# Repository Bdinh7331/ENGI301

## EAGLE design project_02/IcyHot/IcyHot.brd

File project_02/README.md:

Author: Brian Dinh

The goal of this project was to create a PCB of my first project, IcyHot, were I have successfully completed it. Upon consulting with my professor, Erik Welsh, he suggested
that I add in the LED screen that I was unable to integrate during my first project. This project is associated with Rice University's Introduction to Practical Electrical
Engineering course, also known as ENGI 301.

This project uses the following libraries:
1. ENGI301, created by Erik Welsh
2. IcyHot, a custom library created by myself to house the Noctua fan and switch
3. adafruit, which came with EAGLE

To complete this project, I did the following steps:
1. Created a schematic using existing Pocketbeagle, LED screen, and temperature sensors from the three aforementioned libraries.
  -To create the nf-a4x20-5v-pwm (Noctua fan) component, I made a box with 4 pins that was about the physical dimensions of the base of the fan. Since the datasheet did not provide any additional information about how the pins were oriented, I spaced them out by about 100 mil.
  -To create the switch, I followed the exact guidelines provided by its datasheet.
2. Made a board on EAGLE using that schematic. This board was initially 3x4 as suggested by Professor Welsh, but I increased the dimensions to 3.5x4 to fit all of my components.
  -Because of how my components were organized in the board, I routed my components in the top and bottom layers instead of just the top layer.
  -I added as few drill holes as possible, though they were unavoidable because of how the routing was laid out on this board.
3. Prepared a gerber file for manufacturing
  -Exported my IcyHot.brd file as a CAM output, labelling it as "IcyHot_gerber."
  -Downloaded gerbv, an open source gerber reader, to provide a screenshot of the top and bottom layers of the PCB which is located in the "docs" folder of this directory.
  -Created an account at MacroFab.
4. Got quotes for 1, 10, 100, and 1000 PCBs with my components on MacroFab.
  -Substituted another 5V PWM fan for the Noctua because Noctua fans are not available on MacroFab. This affects the price though the fan was not the most expensive component.
  -Prices were much larger than expected since many of the components had very large lead times and/or were not immediately available.

Design Philosophy

  The design philosophy that I used during this project was essentially to keep everything as simple as possible since this is good engineering practice. Because the goal of this project was to put the components that I had used in the first ENGI 301 project onto a PCB, I wanted to replicate the exact components as much as possible. Some specific ways of how I ensured that the schematic would be simple was that I would only create library parts from scratch only when it was absolutely necessary. As several components had schematics, libraries, and boards already available on open source platforms it would be easier, and more accurate, for me to directly copy these materials onto my IcyHot schematic. Moreover, when I created components for the IcyHot library, I focused on making sure I had the necessary pins so that they could be correctly wired to the Pocketbeagle knowing that this wiring would be reflected in the IcyHot board. 
  Because the project's requirements included a second component in my IcyHot library, I chose to make a TPS92411x Floating Switch for Offline AC Linear Direct Drive of LEDs with Low Ripple Current because it paired well with my display screen. My thought was that it would "gatekeep" the voltage level in the system and if it were above a certain level the screen would turn off.

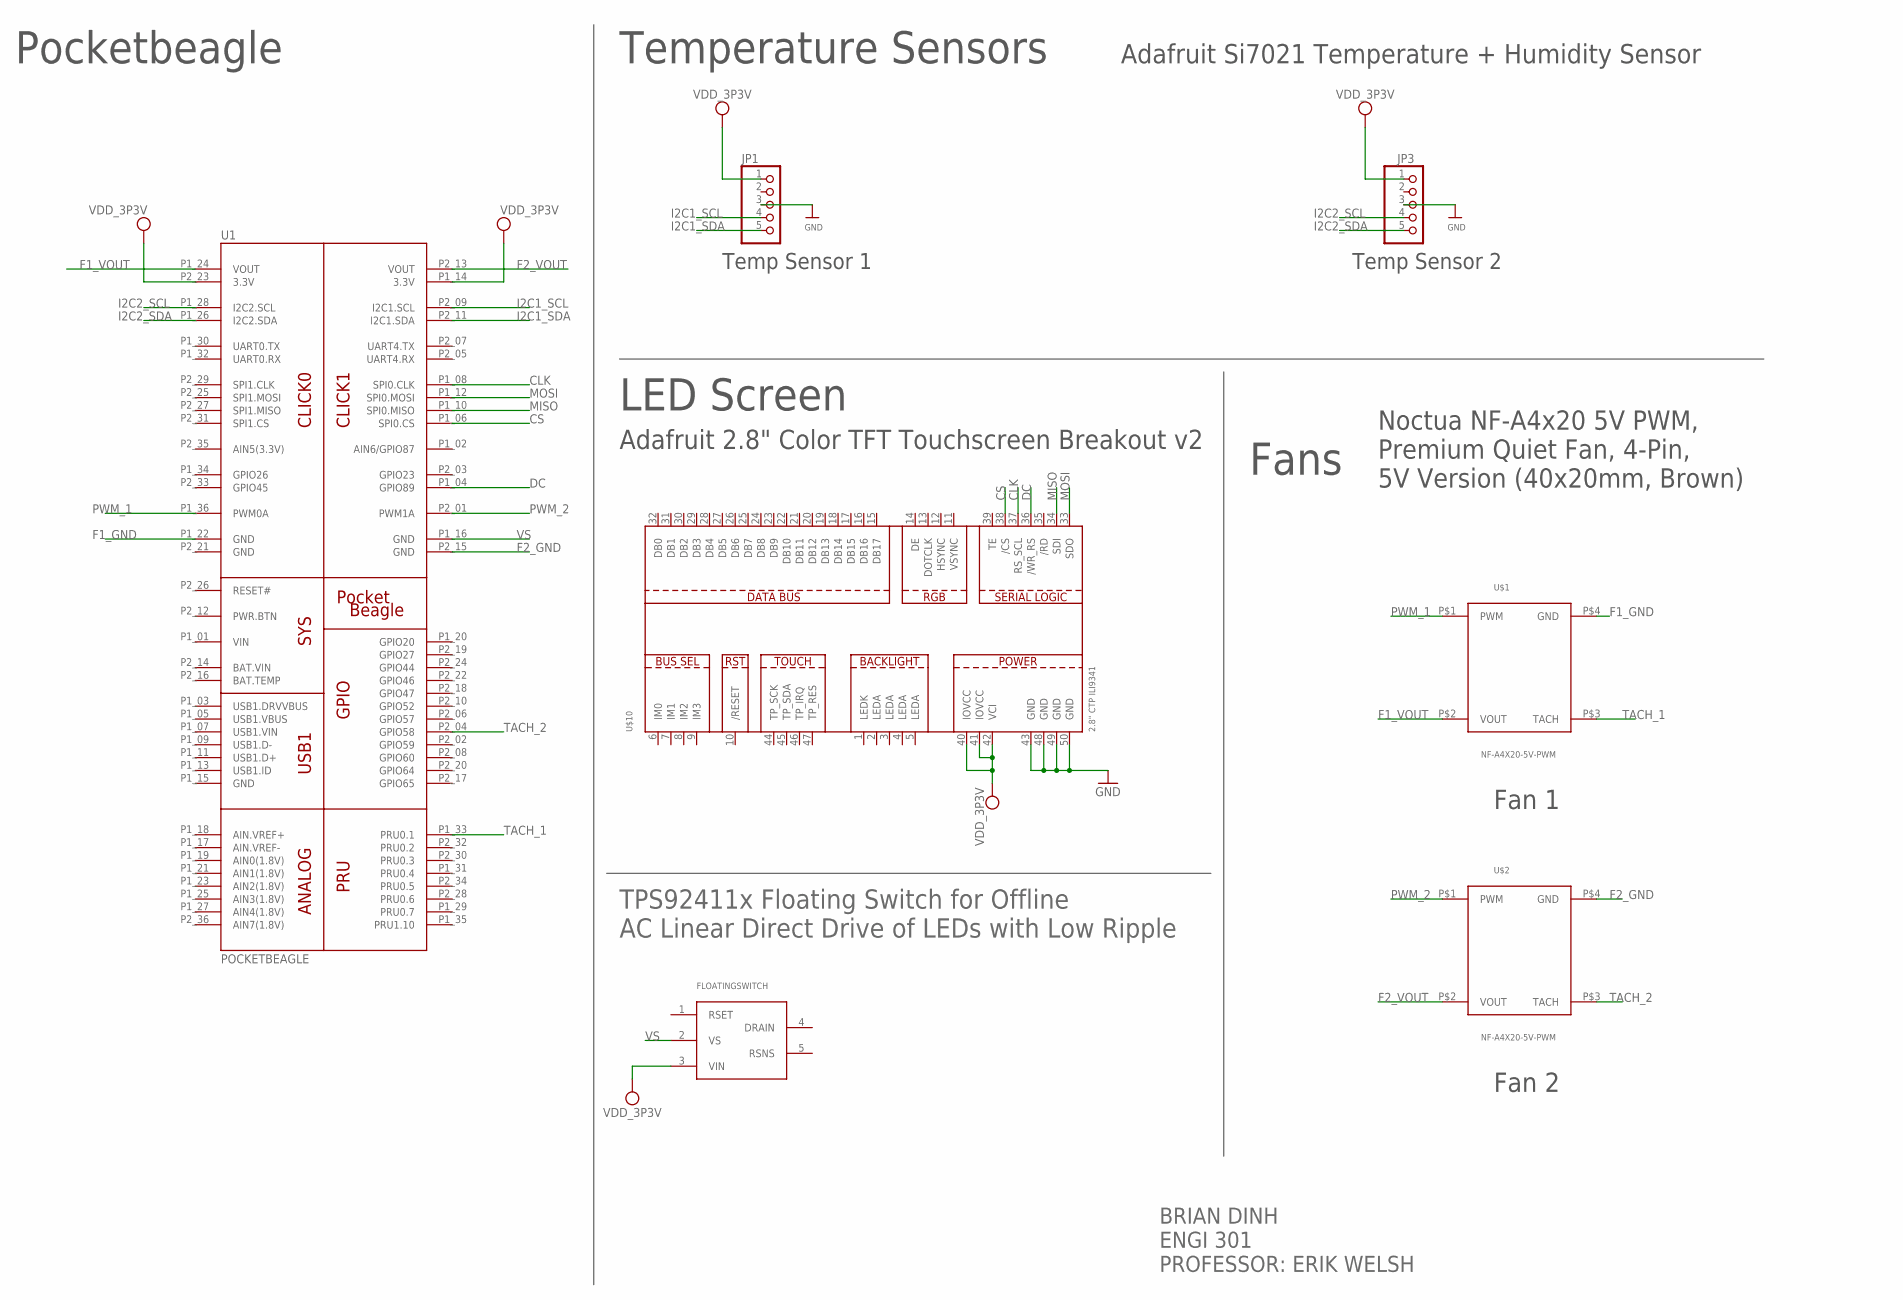
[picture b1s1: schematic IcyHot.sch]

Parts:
FLOATINGSWITCH: TPS92411; SOT23-5
JP1, JP3: HEADER-1X570MIL; 1X05_ROUND_70
U1: POCKETBEAGLE
U$1, U$2: NF-A4X20-5V-PWM
U$10: 2.8" CTP ILI9341; TFT_2.83IN_240X320_50PIN

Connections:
BAT.VIN: U1.P2_14 (BAT.VIN)
CLK: U1.P1_08 (SPI0.CLK), U$10.37 (RS_SCL)
CS: U1.P1_06 (SPI0.CS), U$10.38 (/CS)
DC: U1.P1_04 (GPIO89), U$10.36 (/WR_RS)
F1_GND: U1.P1_22 (GND), U$1.P$4 (GND)
F1_VOUT: U1.P1_24 (VOUT), U$1.P$2 (VOUT)
F2_GND: U1.P2_15 (GND), U$2.P$4 (GND)
F2_VOUT: U1.P2_13 (VOUT), U$2.P$2 (VOUT)
GND: JP1.3, JP3.3, U1.P2_21 (GND), U$10.43 (GND), U$10.48 (GND), U$10.49 (GND), U$10.50 (GND)
I2C1_SCL: JP1.4, U1.P2_09 (I2C1.SCL)
I2C1_SDA: JP1.5, U1.P2_11 (I2C1.SDA)
I2C2_SCL: JP3.4, U1.P1_28 (I2C2.SCL)
I2C2_SDA: JP3.5, U1.P1_26 (I2C2.SDA)
MISO: U1.P1_10 (SPI0.MISO), U$10.34 (SDI)
MOSI: U1.P1_12 (SPI0.MOSI), U$10.33 (SDO)
PWM_1: U1.P1_36 (PWM0A), U$1.P$1 (PWM)
PWM_2: U1.P2_01 (PWM1A), U$2.P$1 (PWM)
TACH_1: U1.P1_33 (PRU0.1), U$1.P$3 (TACH)
TACH_2: U1.P2_04 (GPIO58), U$2.P$3 (TACH)
VDD_3P3V: FLOATINGSWITCH.3 (VIN), JP1.1, JP3.1, U1.P1_14 (3.3V), U1.P2_23 (3.3V), U$10.40 (IOVCC), U$10.41 (IOVCC), U$10.42 (VCI)
VIN: U1.P1_01 (VIN)
VS: FLOATINGSWITCH.2 (VS), U1.P1_16 (GND)

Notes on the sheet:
Pocketbeagle
Temperature Sensors
LED Screen
Temp Sensor 1
Temp Sensor 2
Fans
Adafruit Si7021 Temperature + Humidity Sensor
Adafruit 2.8" Color TFT Touchscreen Breakout v2
Noctua NF-A4x20 5V PWM, Premium Quiet Fan, 4-Pin, 5V Version (40x20mm, Brown)
Fan 1
Fan 2
BRIAN DINH ENGI 301 PROFESSOR: ERIK WELSH
TPS92411x Floating Switch for Offline AC Linear Direct Drive of LEDs with Low Ripple

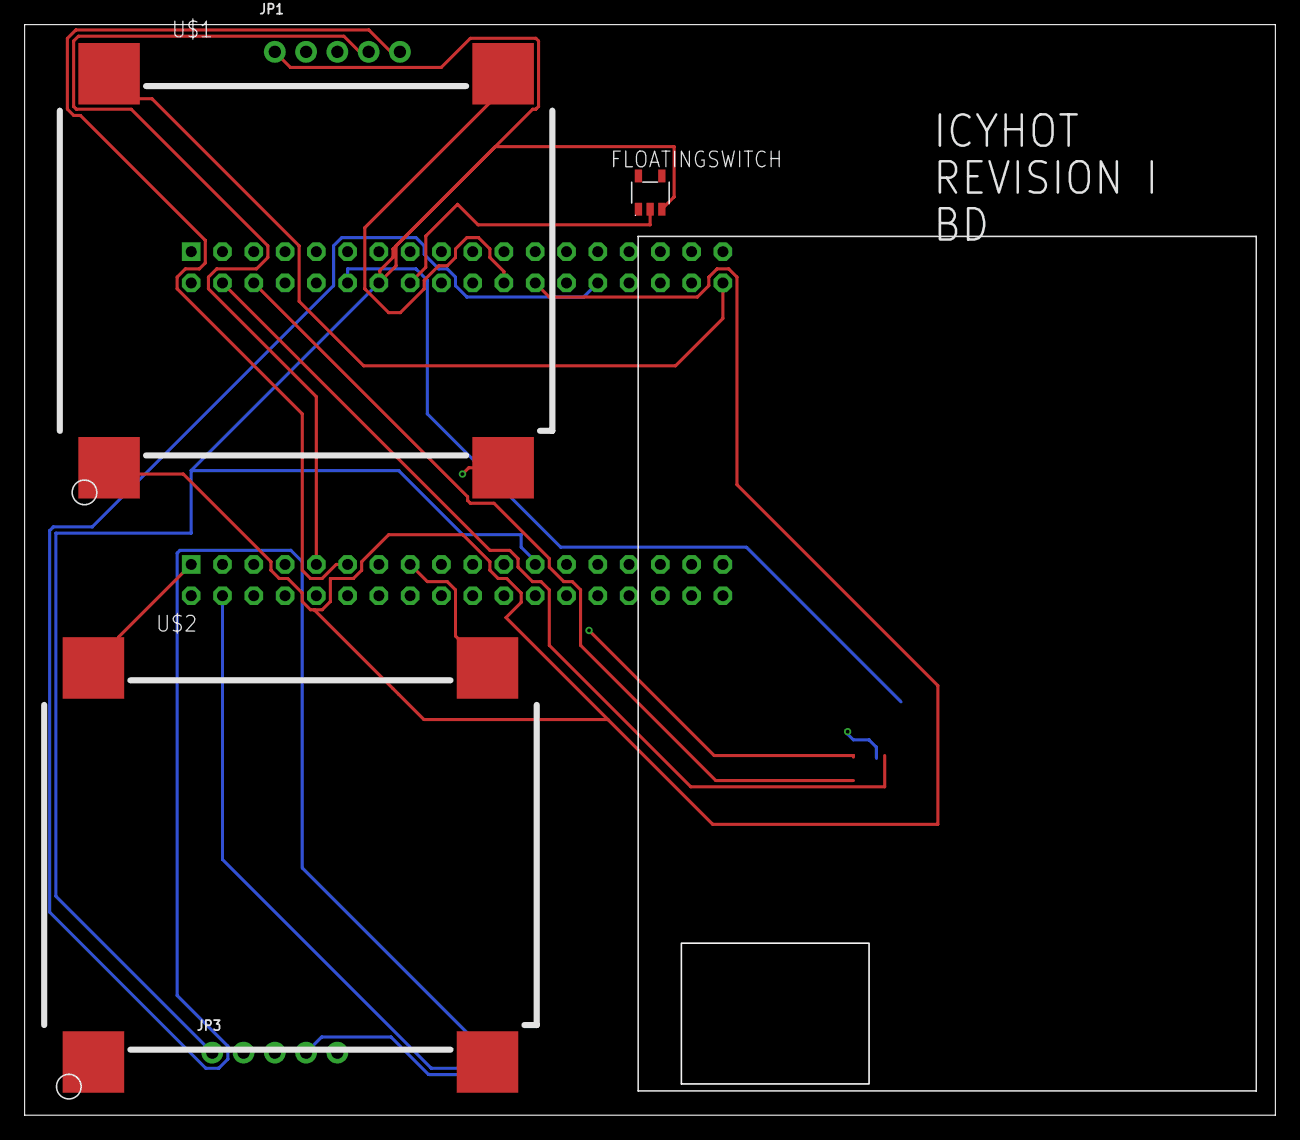
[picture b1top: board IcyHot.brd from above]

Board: 4 copper layers, 101.5 x 88.4 mm, 7 parts (1 on the bottom side), 20 nets.

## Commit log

2020-09-30 ENGI 301 HW4 Q2&3 Submission
2020-11-14 Create project_01
2020-11-14 uploaded project proposal
    changes between this version and the initial version are noted in the PPT
2020-11-14 Create README.txt
    Build instructions and operation instructions
2020-11-23 Create docs
2020-12-16 Create EAGLE
2020-12-19 Delete docs
    deleted to make a folder
2020-12-19 Add files via upload
    Picture of top and bottom layers for Project 2 IcyHot as part of Rice Univeristy's ENGI 301: Intro to Practical Electrical Engineering course.
2020-12-19 Add files via upload
    gerber output
